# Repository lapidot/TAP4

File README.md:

# TAP4
Unibody ergonomic keyboard with 5x3 matrix and 6 key per thumb

Should include Gerber files for 3 layers - bottom, main PCB, and top (maybe even a switchplate which I haven't ordered or used)

QMK folder (with buzzers)
ZMK Folder (with LEDs)

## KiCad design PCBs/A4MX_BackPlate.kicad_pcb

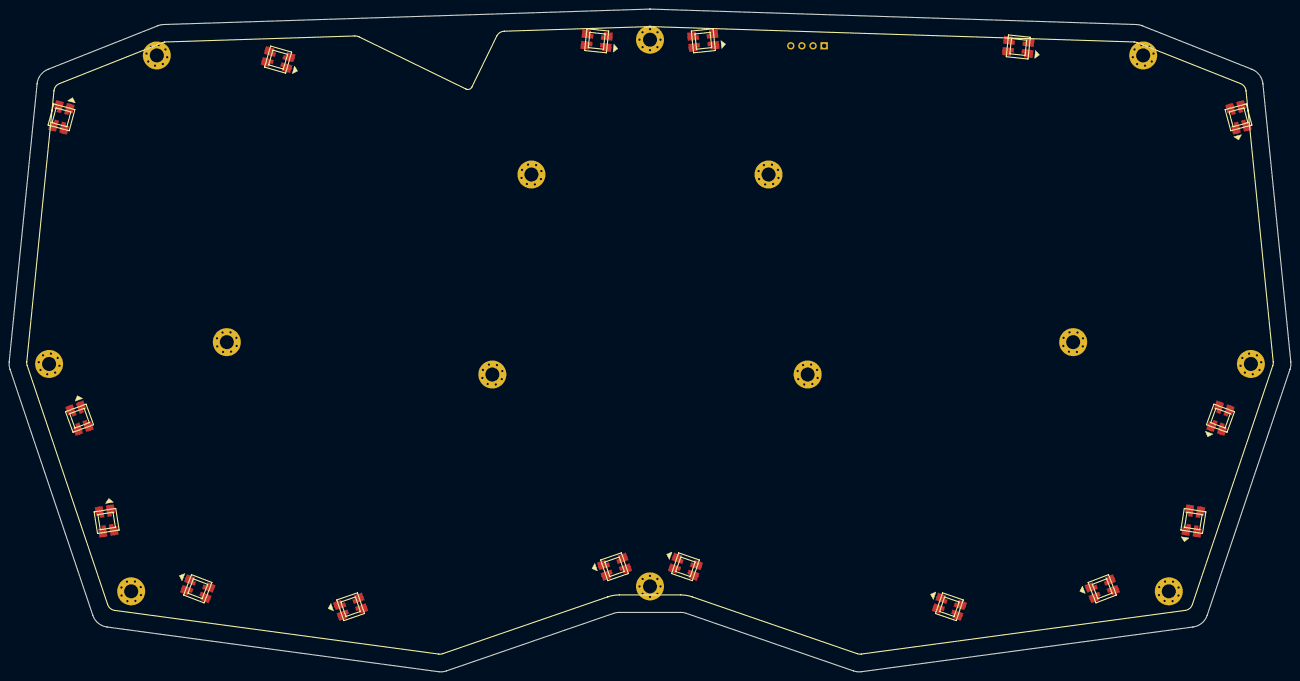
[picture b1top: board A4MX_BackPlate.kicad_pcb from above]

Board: 2 copper layers, 293.0 x 151.5 mm, 31 parts (0 on the bottom side), 21 nets, no tracks yet.

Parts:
LED1, LED2, LED3, LED4, LED5, LED6, LED7, LED8, LED9, LED10, LED11, LED12, LED13, LED14, LED15, LED171: WS2812B
LEDBreakout3Pin1: OLED; OLED_headers
_1, _2, _3, _4, _5, _6, _7, _8, _9, _10, _11, _12, _13, _14: MountingHole_3.2mm_M3_Pad_Via

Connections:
D3: LED171.4, LED171.44, LEDBreakout3Pin1.3
GND: LED1.3, LED1.33, LED2.3, LED2.33, LED3.3, LED3.33, LED4.3, LED4.33, LED5.3, LED5.33, LED6.3, LED6.33, LED7.3, LED7.33, LED8.3, LED8.33, LED9.3, LED9.33, LED10.3, LED10.33, LED11.3, LED11.33, LED12.3, LED12.33, LED13.3, LED13.33, LED14.3, LED14.33, LED15.3, LED15.33, LED171.3, LED171.33, LEDBreakout3Pin1.1
LEDVCC: LED1.1, LED1.11, LED2.1, LED2.11, LED3.1, LED3.11, LED4.1, LED4.11, LED5.1, LED5.11, LED6.1, LED6.11, LED7.1, LED7.11, LED8.1, LED8.11, LED9.1, LED9.11, LED10.1, LED10.11, LED11.1, LED11.11, LED12.1, LED12.11, LED13.1, LED13.11, LED14.1, LED14.11, LED15.1, LED15.11
LEDVCCIN: LED171.1, LED171.11
none: LED1.2, LED1.22
rgbOut01: LED1.4, LED1.44, LED2.2, LED2.22
rgbOut02: LED2.4, LED2.44
rgbOut03: LED3.2, LED3.22
rgbOut04: LED3.4, LED3.44, LED4.2, LED4.22
rgbOut05: LED4.4, LED4.44, LED5.2, LED5.22
rgbOut06: LED5.4, LED5.44, LED6.2, LED6.22
rgbOut07: LED6.4, LED6.44, LED7.2, LED7.22
rgbOut08: LED7.4, LED7.44, LED8.2, LED8.22
rgbOut09: LED8.4, LED8.44, LED9.4, LED9.44
rgbOut10: LED9.2, LED9.22, LED10.4, LED10.44
rgbOut11: LED10.2, LED10.22, LED11.2, LED11.22
rgbOut12: LED11.4, LED11.44, LED12.2, LED12.22
rgbOut13: LED12.4, LED12.44, LED13.2, LED13.22
rgbOut14: LED13.4, LED13.44, LED14.2, LED14.22
rgbOut15: LED14.4, LED14.44, LED15.2, LED15.22
rgbOut16: LED15.4, LED15.44, LED171.2, LED171.22

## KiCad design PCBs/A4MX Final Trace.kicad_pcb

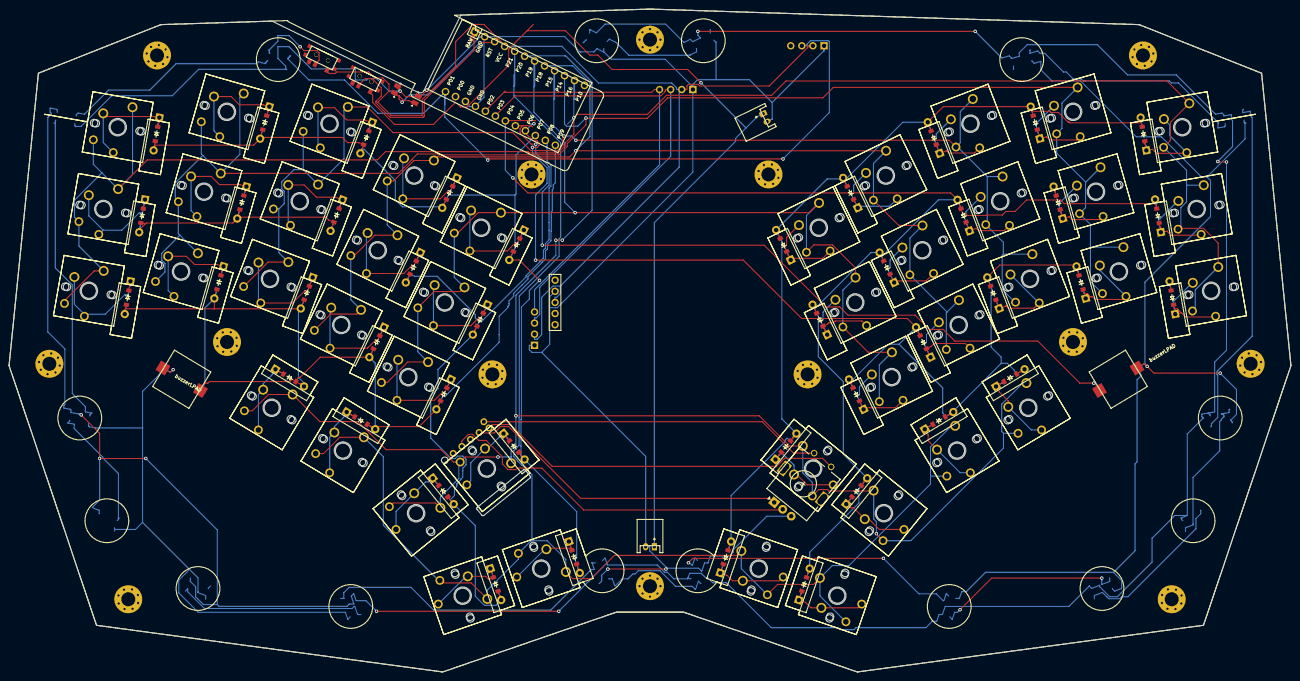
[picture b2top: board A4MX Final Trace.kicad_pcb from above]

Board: 2 copper layers, 293.1 x 151.6 mm, 171 parts (0 on the bottom side), 83 nets.

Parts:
D1, D2, D3, D4, D5, D6, D7, D8, D9, D10, D11, D12, D13, D14, D15, D16, D17, D18, D19, D20, D21, D22, D23, D24, D25, D26, D27, D28, D29, D30, D31, D32, D33, D34, D35, D36, D37, D38, D39, D40, D41, D42: ComboDiode
DISP1: nice_view
JST1, JST2: JST_PH_S2B-PH-K_02x2.00mm_Angled
LED1, LED2, LED3, LED4, LED5, LED6, LED7, LED8, LED9, LED10, LED11, LED12, LED13, LED14, LED15, LED171: WS2812B
LEDBreakout3Pin1: OLED; OLED_headers
M10.001251, M10.001252, M10.001253, M10.001254, M10.001255, M10.001256, M10.001257, M10.001258, M10.001259, M10.0012510, M10.0012511, M10.0012512, M10.0012513, M10.0012514, M10.0012515, M10.0012516, M10.0012517, M10.0012518, M10.0012519, M10.0012520, M10.0012521, M10.0012522, M10.0012523, M10.0012524, M10.0012525, M10.0012526, M10.0012527, M10.0012528, M10.0012529, M10.0012530, M10.0012531, M10.0012532, M10.0012533, M10.0012534, M10.0012535, M10.0012536, M10.0012537, M10.0012538, M10.0012539, M10.0012540, M10.0012541, M10.0012542: MX
M10.0012543, M10.0012544, M10.0012545, M10.0012546, M10.0012547, M10.0012548, M10.0012549, M10.0012550, M10.0012551, M10.0012552, M10.0012553, M10.0012554, M10.0012555, M10.0012556, M10.0012557, M10.0012558, M10.0012559, M10.0012560, M10.0012561, M10.0012562, M10.0012563, M10.0012564, M10.0012565, M10.0012566, M10.0012567, M10.0012568, M10.0012569, M10.0012570, M10.0012571, M10.0012572, M10.0012573, M10.0012574, M10.0012575, M10.0012576, M10.0012577, M10.0012578, M10.0012579, M10.0012580, M10.0012581, M10.0012582, M10.0012583, M10.0012584: PG1350
MCU1: ProMicro
OLED1, OLED2: OLED; OLED_headers
PAD1, PAD2, PAD3, PAD4: SMDPad
ROT1: rotary_encoder
RST1: reset_button_smd_side
T1, T2: SPDT_C128955
_1, _2, _3, _4, _5, _6, _7, _8, _9, _10, _11, _12, _13, _14: MountingHole_3.2mm_M3_Pad_Via

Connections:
GND: DISP1.2, JST1.2, JST2.2, LED1.3, LED1.33, LED2.3, LED2.33, LED3.3, LED3.33, LED4.3, LED4.33, LED5.3, LED5.33, LED6.3, LED6.33, LED7.3, LED7.33, LED8.3, LED8.33, LED9.3, LED9.33, LED10.3, LED10.33, LED11.3, LED11.33, LED12.3, LED12.33, LED13.3, LED13.33, LED14.3, LED14.33, LED15.3, LED15.33, LED171.3, LED171.33, LEDBreakout3Pin1.1, MCU1.2, MCU1.15, MCU1.16, OLED1.1, OLED2.1, PAD1.1, PAD3.1, ROT1.B, RST1.1, RST1.3
LEDVCC: LED1.1, LED1.11, LED2.1, LED2.11, LED3.1, LED3.11, LED4.1, LED4.11, LED5.1, LED5.11, LED6.1, LED6.11, LED7.1, LED7.11, LED8.1, LED8.11, LED9.1, LED9.11, LED10.1, LED10.11, LED11.1, LED11.11, LED12.1, LED12.11, LED13.1, LED13.11, LED14.1, LED14.11, LED15.1, LED15.11
LEDVCCIN: LED171.1, LED171.11, T2.2
P00: D8.2, D10.2, D30.2, D33.2, D36.2, D39.2, D42.2
P1: LED171.4, LED171.44, LEDBreakout3Pin1.3, MCU1.13
P2: MCU1.17, OLED1.4, OLED2.4
P3: MCU1.18, OLED1.3, OLED2.3
P4: D7.2, D9.2, D29.2, D32.2, D35.2, D38.2, D41.2, MCU1.19
P5: MCU1.20, PAD4.1
P6: D11.2, D12.2, D28.2, D31.2, D34.2, D37.2, D40.2, MCU1.21
P7: D2.2, D4.2, D15.2, D18.2, D21.2, D24.2, D27.2, MCU1.22
P8: D1.2, D3.2, D14.2, D17.2, D20.2, D23.2, D26.2, MCU1.23
P9: D5.2, D6.2, D13.2, D16.2, D19.2, D22.2, D25.2, MCU1.24, PAD2.1
P14: M10.001254.1, M10.001255.1, M10.001256.1, M10.0012525.1, M10.0012526.1, M10.0012527.1, M10.0012546.1, M10.0012547.1, M10.0012548.1, M10.0012567.1, M10.0012568.1, M10.0012569.1, MCU1.10
P15: M10.001257.1, M10.001258.1, M10.001259.1, M10.0012528.1, M10.0012529.1, M10.0012530.1, M10.0012549.1, M10.0012550.1, M10.0012551.1, M10.0012570.1, M10.0012571.1, M10.0012572.1, MCU1.9
P16: M10.001251.1, M10.001252.1, M10.001253.1, M10.0012522.1, M10.0012523.1, M10.0012524.1, M10.0012543.1, M10.0012544.1, M10.0012545.1, M10.0012564.1, M10.0012565.1, M10.0012566.1, MCU1.11
P18: M10.0012510.1, M10.0012511.1, M10.0012512.1, M10.0012531.1, M10.0012532.1, M10.0012533.1, M10.0012552.1, M10.0012553.1, M10.0012554.1, M10.0012573.1, M10.0012574.1, M10.0012575.1, MCU1.8
P19: M10.0012513.1, M10.0012514.1, M10.0012515.1, M10.0012534.1, M10.0012535.1, M10.0012536.1, M10.0012555.1, M10.0012556.1, M10.0012557.1, M10.0012576.1, M10.0012577.1, M10.0012578.1, MCU1.7
P20: M10.0012516.1, M10.0012517.1, M10.0012520.1, M10.0012537.1, M10.0012538.1, M10.0012541.1, M10.0012558.1, M10.0012559.1, M10.0012562.1, M10.0012579.1, M10.0012580.1, M10.0012583.1, MCU1.6
P21: M10.0012518.1, M10.0012519.1, M10.0012521.1, M10.0012539.1, M10.0012540.1, M10.0012542.1, M10.0012560.1, M10.0012561.1, M10.0012563.1, M10.0012581.1, M10.0012582.1, M10.0012584.1, MCU1.5
RAW: MCU1.1, T1.2
RST: MCU1.3, RST1.2, RST1.4
VCC: DISP1.3, LEDBreakout3Pin1.2, MCU1.4, OLED1.2, OLED2.2, T2.1
index_bottom: D22.1, M10.0012510.2, M10.0012552.2
index_home: D23.1, M10.0012511.2, M10.0012553.2
index_top: D24.1, M10.0012512.2, M10.0012554.2
inner_bottom: D25.1, M10.0012513.2, M10.0012555.2
inner_home: D26.1, M10.0012514.2, M10.0012556.2
inner_top: D27.1, M10.0012515.2, M10.0012557.2
middle_bottom: D19.1, M10.001257.2, M10.0012549.2
middle_home: D20.1, M10.001258.2, M10.0012550.2
middle_top: D21.1, M10.001259.2, M10.0012551.2
mirror_index_bottom: D37.1, M10.0012531.2, M10.0012573.2
mirror_index_home: D38.1, M10.0012532.2, M10.0012574.2
mirror_index_top: D39.1, M10.0012533.2, M10.0012575.2
mirror_inner_bottom: D40.1, M10.0012534.2, M10.0012576.2
mirror_inner_home: D41.1, M10.0012535.2, M10.0012577.2
mirror_inner_top: D42.1, M10.0012536.2, M10.0012578.2
mirror_middle_bottom: D34.1, M10.0012528.2, M10.0012570.2
mirror_middle_home: D35.1, M10.0012529.2, M10.0012571.2
mirror_middle_top: D36.1, M10.0012530.2, M10.0012572.2
mirror_pinky_bottom: D28.1, M10.0012522.2, M10.0012564.2
mirror_pinky_home: D29.1, M10.0012523.2, M10.0012565.2
mirror_pinky_top: D30.1, M10.0012524.2, M10.0012566.2
mirror_reachy_rob: D9.1, M10.0012539.2, M10.0012581.2
mirror_reachy_tob: D10.1, M10.0012540.2, M10.0012582.2
mirror_ring_bottom: D31.1, M10.0012525.2, M10.0012567.2
mirror_ring_home: D32.1, M10.0012526.2, M10.0012568.2
mirror_ring_top: D33.1, M10.0012527.2, M10.0012569.2
mirror_thomr_rob: D7.1, M10.0012537.2, M10.0012579.2
mirror_thomr_tob: D8.1, M10.0012538.2, M10.0012580.2
mirror_tucky_default: D12.1, M10.0012542.2, M10.0012584.2
mirror_tuckyy_default: D11.1, M10.0012541.2, M10.0012583.2
none: LED13.2, LED13.22
pinky_bottom: D13.1, M10.001251.2, M10.0012543.2
pinky_home: D14.1, M10.001252.2, M10.0012544.2
pinky_top: D15.1, M10.001253.2, M10.0012545.2
pos: JST1.1, JST2.1, T1.1
reachy_rob: D3.1, M10.0012518.2, M10.0012560.2
reachy_tob: D4.1, M10.0012519.2, M10.0012561.2
rgbOut01: LED12.2, LED12.22, LED13.4, LED13.44
rgbOut02: LED12.4, LED12.44
rgbOut03: LED3.2, LED3.22
rgbOut04: LED3.4, LED3.44, LED15.2, LED15.22
rgbOut05: LED9.2, LED9.22, LED15.4, LED15.44
rgbOut06: LED5.2, LED5.22, LED9.4, LED9.44
rgbOut07: LED5.4, LED5.44, LED7.2, LED7.22
rgbOut08: LED7.4, LED7.44, LED11.2, LED11.22
rgbOut09: LED2.4, LED2.44, LED11.4, LED11.44
rgbOut10: LED1.4, LED1.44, LED2.2, LED2.22
rgbOut11: LED1.2, LED1.22, LED10.2, LED10.22
rgbOut12: LED6.2, LED6.22, LED10.4, LED10.44
rgbOut13: LED4.2, LED4.22, LED6.4, LED6.44
rgbOut14: LED4.4, LED4.44, LED8.2, LED8.22
rgbOut15: LED8.4, LED8.44, LED14.2, LED14.22
rgbOut16: LED14.4, LED14.44, LED171.2, LED171.22
ring_bottom: D16.1, M10.001254.2, M10.0012546.2
ring_home: D17.1, M10.001255.2, M10.0012547.2
ring_top: D18.1, M10.001256.2, M10.0012548.2
thomr_rob: D1.1, M10.0012516.2, M10.0012558.2
thomr_tob: D2.1, M10.0012517.2, M10.0012559.2
tucky_default: D6.1, M10.0012521.2, M10.0012563.2
tuckyy_default: D5.1, M10.0012520.2, M10.0012562.2

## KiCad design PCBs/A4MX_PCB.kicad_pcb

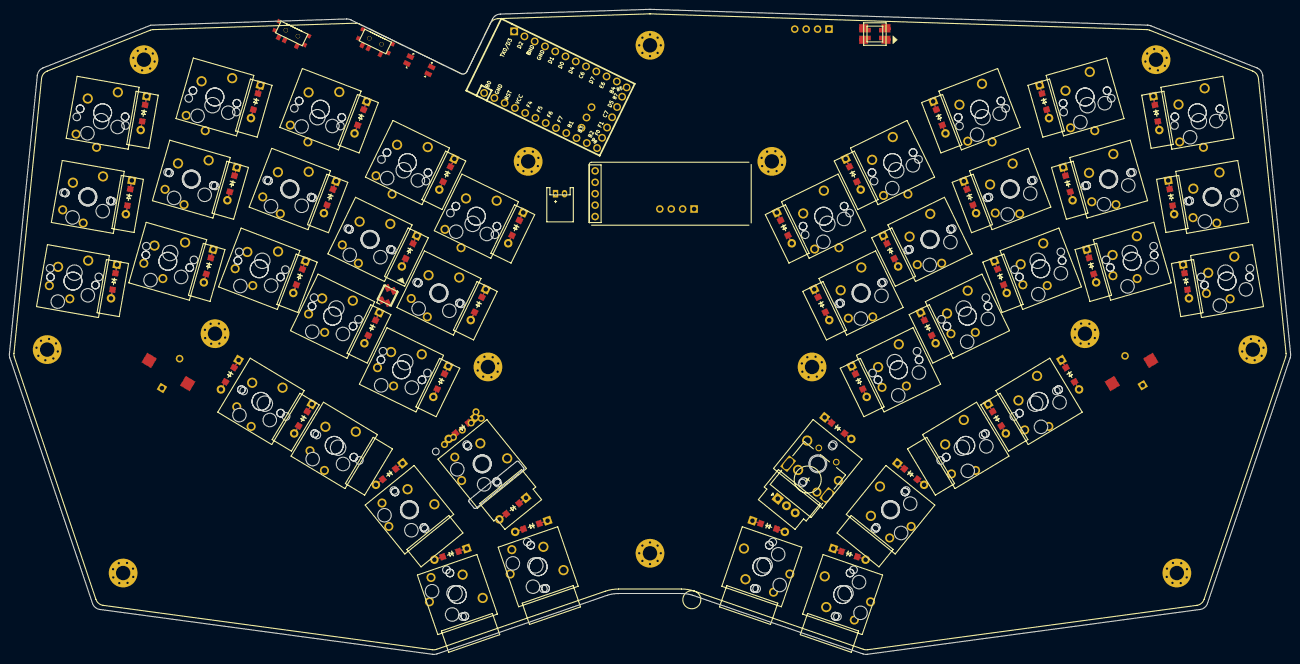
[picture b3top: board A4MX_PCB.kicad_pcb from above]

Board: 2 copper layers, 284.9 x 143.4 mm, 216 parts (0 on the bottom side), 88 nets, no tracks yet.

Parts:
BUZZER1, BUZZER2: BUZZER; Buzzer_12x9.5RM7.6
C10.0012584, C10.0012585, C10.0012586, C10.0012587, C10.0012588, C10.0012589, C10.0012590, C10.0012591, C10.0012592, C10.0012593, C10.0012594, C10.0012595, C10.0012596, C10.0012597, C10.0012598, C10.0012599, C10.00125100, C10.00125101, C10.00125102, C10.00125103, C10.00125104, C10.00125105, C10.00125106, C10.00125107, C10.00125108, C10.00125109, C10.00125110, C10.00125111, C10.00125112, C10.00125113, C10.00125114, C10.00125115, C10.00125116, C10.00125117, C10.00125118, C10.00125119, C10.00125120, C10.00125121, C10.00125122, C10.00125123, C10.00125124, C10.00125125: PG1350
D1, D2, D3, D4, D5, D6, D7, D8, D9, D10, D11, D12, D13, D14, D15, D16, D17, D18, D19, D20, D21, D22, D23, D24, D25, D26, D27, D28, D29, D30, D31, D32, D33, D34, D35, D36, D37, D38, D39, D40, D41, D42, D43: ComboDiode
DISP1: nice_view
J1: Jumper
JST1: JST_PH_S2B-PH-K_02x2.00mm_Angled
LED1, LED4, LED5, LED6, LED7, LED8, LED9, LED10, LED11, LED12, LED13, LED14, LED15, LED16, LED17, LED18, LED171: WS2812B
LED2: LED_Avago_PLCC4_3.2x2.8mm_CW
LEDBreakout3Pin1: OLED; OLED_headers
M10.001251, M10.001252, M10.001253, M10.001254, M10.001255, M10.001256, M10.001257, M10.001258, M10.001259, M10.0012510, M10.0012511, M10.0012512, M10.0012513, M10.0012514, M10.0012515, M10.0012516, M10.0012517, M10.0012518, M10.0012519, M10.0012520, M10.0012521, M10.0012522, M10.0012523, M10.0012524, M10.0012525, M10.0012526, M10.0012527, M10.0012528, M10.0012529, M10.0012530, M10.0012531, M10.0012532, M10.0012533, M10.0012534, M10.0012535, M10.0012536, M10.0012537, M10.0012538, M10.0012539, M10.0012540, M10.0012541, M10.0012542, M10.0012543, M10.0012544, M10.0012545, M10.0012546, M10.0012547, M10.0012548, M10.0012549, M10.0012550, M10.0012551, M10.0012552, M10.0012553, M10.0012554, M10.0012555, M10.0012556, M10.0012557, M10.0012558, M10.0012559, M10.0012560, M10.0012561, M10.0012562, M10.0012563, M10.0012564, M10.0012565, M10.0012566, M10.0012567, M10.0012568, M10.0012569, M10.0012570, M10.0012571, M10.0012572, M10.0012573, M10.0012574, M10.0012575, M10.0012576, M10.0012577, M10.0012578, M10.0012579, M10.0012580, M10.0012581, M10.0012582, M10.0012583: MX
MCU1: Elite-C; Elite-C&NiceNano
OLED1: OLED; OLED_headers
PAD1, PAD2, PAD3, PAD4: SMDPad
ROT1: rotary_encoder
RST1: reset_button_smd_side
T1, T2: SPDT_C128955
_1, _2, _3, _4, _5, _6, _7, _8, _9, _10, _11, _12, _13, _14: MountingHole_3.2mm_M3_Pad_Via

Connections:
B1: C10.0012586.1, C10.0012591.1, C10.0012596.1, C10.00125101.1, C10.00125106.1, C10.00125111.1, M10.001257.1, M10.001258.1, M10.001259.1, M10.0012528.1, M10.0012529.1, M10.0012530.1, M10.0012549.2, M10.0012550.2, M10.0012551.2, M10.0012570.2, M10.0012571.2, M10.0012572.2, MCU1.16
B2: C10.0012584.1, C10.0012589.1, C10.0012594.1, C10.0012599.1, C10.00125104.1, C10.00125109.1, M10.001251.1, M10.001252.1, M10.001253.1, M10.0012522.1, M10.0012523.1, M10.0012524.1, M10.0012543.2, M10.0012544.2, M10.0012545.2, M10.0012564.2, M10.0012565.2, M10.0012566.2, MCU1.14
B3: C10.0012585.1, C10.0012590.1, C10.0012595.1, C10.00125100.1, C10.00125105.1, C10.00125110.1, M10.001254.1, M10.001255.1, M10.001256.1, M10.0012525.1, M10.0012526.1, M10.0012527.1, M10.0012546.2, M10.0012547.2, M10.0012548.2, M10.0012567.2, M10.0012568.2, M10.0012569.2, MCU1.15
B4: D2.2, D5.2, D8.2, D11.2, D14.2, D31.2, D33.2, MCU1.11
B5: D1.2, D4.2, D7.2, D10.2, D13.2, D35.2, D36.2, MCU1.12
B6: BUZZER1.2, MCU1.13, PAD2.1
C6: BUZZER2.2, MCU1.8, PAD4.1
D0: MCU1.6, OLED1.3
D1: DISP1.1, MCU1.5, OLED1.4
D2: D18.2, D21.2, D24.2, D27.2, D30.2, D38.2, D40.2, MCU1.2
D3: LED171.4, LED171.44, LEDBreakout3Pin1.3, MCU1.1
D4: D17.2, D20.2, D23.2, D26.2, D29.2, D37.2, D39.2, MCU1.7
D5: LED1.4, LED1.44, MCU1.26, MCU1.33
D7: D16.2, D19.2, D22.2, D25.2, D28.2, D41.2, D42.2, MCU1.9
E6: D3.2, D6.2, D9.2, D12.2, D15.2, D32.2, D34.2, D43.2, MCU1.10
F0: MCU1.29, MCU1.31, ROT1.A
F1: MCU1.28, MCU1.32, ROT1.C
F4: C10.00125115.1, C10.00125117.1, C10.00125122.1, C10.00125123.1, C10.00125124.1, C10.00125125.1, M10.0012518.1, M10.0012519.1, M10.0012521.1, M10.0012539.1, M10.0012540.1, M10.0012542.1, M10.0012560.2, M10.0012561.2, M10.0012563.2, M10.0012580.2, M10.0012581.2, M10.0012583.2, MCU1.20
F5: C10.00125114.1, C10.00125116.1, C10.00125118.1, C10.00125119.1, C10.00125120.1, C10.00125121.1, M10.0012516.1, M10.0012517.1, M10.0012520.1, M10.0012537.1, M10.0012538.1, M10.0012541.1, M10.0012558.2, M10.0012559.2, M10.0012562.2, M10.0012579.2, M10.0012582.2, MCU1.19, ROT1.1
F6: C10.0012588.1, C10.0012593.1, C10.0012598.1, C10.00125103.1, C10.00125108.1, C10.00125113.1, M10.0012513.1, M10.0012514.1, M10.0012515.1, M10.0012534.1, M10.0012535.1, M10.0012536.1, M10.0012555.2, M10.0012556.2, M10.0012557.2, M10.0012576.2, M10.0012577.2, M10.0012578.2, MCU1.18
F7: C10.0012587.1, C10.0012592.1, C10.0012597.1, C10.00125102.1, C10.00125107.1, C10.00125112.1, M10.0012510.1, M10.0012511.1, M10.0012512.1, M10.0012531.1, M10.0012532.1, M10.0012533.1, M10.0012552.2, M10.0012553.2, M10.0012554.2, M10.0012573.2, M10.0012574.2, M10.0012575.2, MCU1.17
GND: BUZZER1.1, BUZZER2.1, DISP1.2, JST1.2, LED1.3, LED1.33, LED2.3, LED4.3, LED4.33, LED5.3, LED5.33, LED6.3, LED6.33, LED7.3, LED7.33, LED8.3, LED8.33, LED9.3, LED9.33, LED10.3, LED10.33, LED11.3, LED11.33, LED12.3, LED12.33, LED13.3, LED13.33, LED14.3, LED14.33, LED15.3, LED15.33, LED16.3, LED16.33, LED17.3, LED17.33, LED18.3, LED18.33, LED171.3, LED171.33, LEDBreakout3Pin1.1, MCU1.3, MCU1.4, MCU1.23, OLED1.1, PAD1.1, PAD3.1, ROT1.B, RST1.1, RST1.3
LEDVCC: LED4.1, LED4.11, LED5.1, LED5.11, LED6.1, LED6.11, LED7.1, LED7.11, LED8.1, LED8.11, LED9.1, LED9.11, LED10.1, LED10.11, LED11.1, LED11.11, LED12.1, LED12.11, LED13.1, LED13.11, LED14.1, LED14.11, LED15.1, LED15.11, LED16.1, LED16.11, LED17.1, LED17.11, LED18.1, LED18.11
LEDVCCIN: LED171.1, LED171.11, T2.2
RST: MCU1.22, RST1.2, RST1.4
TopLEDVCC: J1.2, LED1.1, LED1.11, LED2.1
VCC: DISP1.3, J1.1, LEDBreakout3Pin1.2, MCU1.21, OLED1.2, T1.2, T2.1
deadEnd: LED1.2, LED1.22
index_bottom: C10.00125107.2, D10.1, M10.0012510.2, M10.0012552.1
index_home: C10.0012597.2, D11.1, M10.0012511.2, M10.0012553.1
index_top: C10.0012587.2, D12.1, M10.0012512.2, M10.0012554.1
inner_bottom: C10.00125108.2, D13.1, M10.0012513.2, M10.0012555.1
inner_home: C10.0012598.2, D14.1, M10.0012514.2, M10.0012556.1
inner_top: C10.0012588.2, D15.1, M10.0012515.2, M10.0012557.1
middle_bottom: C10.00125106.2, D7.1, M10.001257.2, M10.0012549.1
middle_home: C10.0012596.2, D8.1, M10.001258.2, M10.0012550.1
middle_top: C10.0012586.2, D9.1, M10.001259.2, M10.0012551.1
mirror_index_bottom: C10.00125112.2, D25.1, M10.0012531.2, M10.0012573.1
mirror_index_home: C10.00125102.2, D26.1, M10.0012532.2, M10.0012574.1
mirror_index_top: C10.0012592.2, D27.1, M10.0012533.2, M10.0012575.1
mirror_inner_bottom: C10.00125113.2, D28.1, M10.0012534.2, M10.0012576.1
mirror_inner_home: C10.00125103.2, D29.1, M10.0012535.2, M10.0012577.1
mirror_inner_top: C10.0012593.2, D30.1, M10.0012536.2, M10.0012578.1
mirror_middle_bottom: C10.00125111.2, D22.1, M10.0012528.2, M10.0012570.1
mirror_middle_home: C10.00125101.2, D23.1, M10.0012529.2, M10.0012571.1
mirror_middle_top: C10.0012591.2, D24.1, M10.0012530.2, M10.0012572.1
mirror_pinky_bottom: C10.00125109.2, D16.1, M10.0012522.2, M10.0012564.1
mirror_pinky_home: C10.0012599.2, D17.1, M10.0012523.2, M10.0012565.1
mirror_pinky_top: C10.0012589.2, D18.1, M10.0012524.2, M10.0012566.1
mirror_reachy_bob: C10.00125124.2, D39.1, M10.0012539.2, M10.0012580.1
mirror_reachy_tob: C10.00125125.2, D40.1, M10.0012540.2, M10.0012581.1
mirror_ring_bottom: C10.00125110.2, D19.1, M10.0012525.2, M10.0012567.1
mirror_ring_home: C10.00125100.2, D20.1, M10.0012526.2, M10.0012568.1
mirror_ring_top: C10.0012590.2, D21.1, M10.0012527.2, M10.0012569.1
mirror_thomr_bob: C10.00125120.2, D37.1, M10.0012537.2, M10.0012579.1
mirror_thomr_tob: C10.00125121.2, D38.1, M10.0012538.2, ROT1.2
mirror_tucky_default: C10.00125117.2, D42.1, M10.0012542.2, M10.0012583.1
mirror_tuckyy_default: C10.00125116.2, D41.1, M10.0012541.2, M10.0012582.1
none: LED4.2, LED4.22
pinky_bottom: C10.00125104.2, D1.1, M10.001251.2, M10.0012543.1
pinky_home: C10.0012594.2, D2.1, M10.001252.2, M10.0012544.1
pinky_top: C10.0012584.2, D3.1, M10.001253.2, M10.0012545.1
pos: JST1.1, T1.1
reachy_bob: C10.00125122.2, D33.1, M10.0012518.2, M10.0012560.1
reachy_tob: C10.00125123.2, D34.1, M10.0012519.2, M10.0012561.1
rgbOut01: LED4.4, LED4.44, LED5.2, LED5.22
rgbOut02: LED5.4, LED5.44
rgbOut03: LED6.2, LED6.22
rgbOut04: LED6.4, LED6.44, LED7.2, LED7.22
rgbOut05: LED7.4, LED7.44, LED8.2, LED8.22
rgbOut06: LED8.4, LED8.44, LED9.2, LED9.22
rgbOut07: LED9.4, LED9.44, LED10.2, LED10.22
rgbOut08: LED10.4, LED10.44, LED11.2, LED11.22
rgbOut09: LED11.4, LED11.44, LED12.4, LED12.44
rgbOut10: LED12.2, LED12.22, LED13.4, LED13.44
rgbOut11: LED13.2, LED13.22, LED14.2, LED14.22
rgbOut12: LED14.4, LED14.44, LED15.2, LED15.22
rgbOut13: LED15.4, LED15.44, LED16.2, LED16.22
rgbOut14: LED16.4, LED16.44, LED17.2, LED17.22
rgbOut15: LED17.4, LED17.44, LED18.2, LED18.22
rgbOut16: LED18.4, LED18.44, LED171.2, LED171.22
ring_bottom: C10.00125105.2, D4.1, M10.001254.2, M10.0012546.1
ring_home: C10.0012595.2, D5.1, M10.001255.2, M10.0012547.1
ring_top: C10.0012585.2, D6.1, M10.001256.2, M10.0012548.1
thomr_bob: C10.00125118.2, D31.1, M10.0012516.2, M10.0012558.1
thomr_tob: C10.00125119.2, D32.1, D43.1, M10.0012517.2, M10.0012559.1
tucky_default: C10.00125115.2, D36.1, M10.0012521.2, M10.0012563.1
tuckyy_default: C10.00125114.2, D35.1, M10.0012520.2, M10.0012562.1

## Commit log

2024-08-20 Ergogen YAML and Footprint files
2025-02-05 addded PCBs
2025-02-05 removed A4MX_PCB.kicad_pcb
